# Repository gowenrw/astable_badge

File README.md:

# astable_badge
BSidesDFW 2021 Badge - Astable Multivibrator - Learn To Solder/Electronics/DIY

This is where all the files for the astable_badge will be stored.  
This includes code and art and cad and fab files.  All the things.

## File Structure

This is the file structure of this repository

* [/](/README.md) - YOU ARE HERE
* [/art/](./art/) - Artwork and other graphics created by this project
* [/code/](./code/) - All project related Code / Firmware
* [/docs/](./docs/) - Documentation created by this project including web pages
* [/eda/](./eda/) - Electronic Design Automation files (i.e. KiCad)
* [/reference_parts/](./reference_parts/) - Documentation pulled from other sources related to components (this is a submodule, see below)
* [./README.md](/README.md) - This File
* [./LICENSE](/LICENSE) - Currently set to MIT

Note: the reference_parts directory a link to a submodule repository.
To add it use the following cmd after downloading this template:
```
git submodule add https://github.com/gowenrw/reference_parts reference_parts
```
This will make a link to the current commit of that repo.
To update it to a newer commit after its been added use this cmd:
```
git submodule update --recursive
```

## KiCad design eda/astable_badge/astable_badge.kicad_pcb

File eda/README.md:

# Electronic Design Automation

This is where all the Electronic Design Automation files for the PCB(s) will be stored.
The EDA used is KiCad 5.x unless otherwise specified.

The KiCad projects have been configured to use local libraries for long term sustainability per the best practices listed [HERE](https://hackaday.com/2017/05/18/kicad-best-practises-library-management/) and elsewhere.

## File Structure

This is the file structure of this repository

* [/](/README.md) - Home
* [/eda](/eda/) - YOU ARE HERE
  * /eda/astable_badge/ - KiCad project folder for the badge PCB
    * ./3d_models/ - This directory contains footprint 3d model files
    * ./gerber/ - This directory contains gerber formatted files for manufacturing
    * ./lib_fp/ - This directory contains footprint module directories
    * ./lib_sh/ - This directory contains schematic library files
    * ./snapshots/ - This directory contains prints of schematic / cad files and images of preview / final product
  * /eda/astable_dev/ - KiCad project folder for the development PCB
    * ./3d_models/ - This directory contains footprint 3d model files
    * ./gerber/ - This directory contains gerber formatted files for manufacturing
    * ./lib_fp/ - This directory contains footprint module directories
    * ./lib_sh/ - This directory contains schematic library files
    * ./snapshots/ - This directory contains prints of schematic / cad files and images of preview / final product

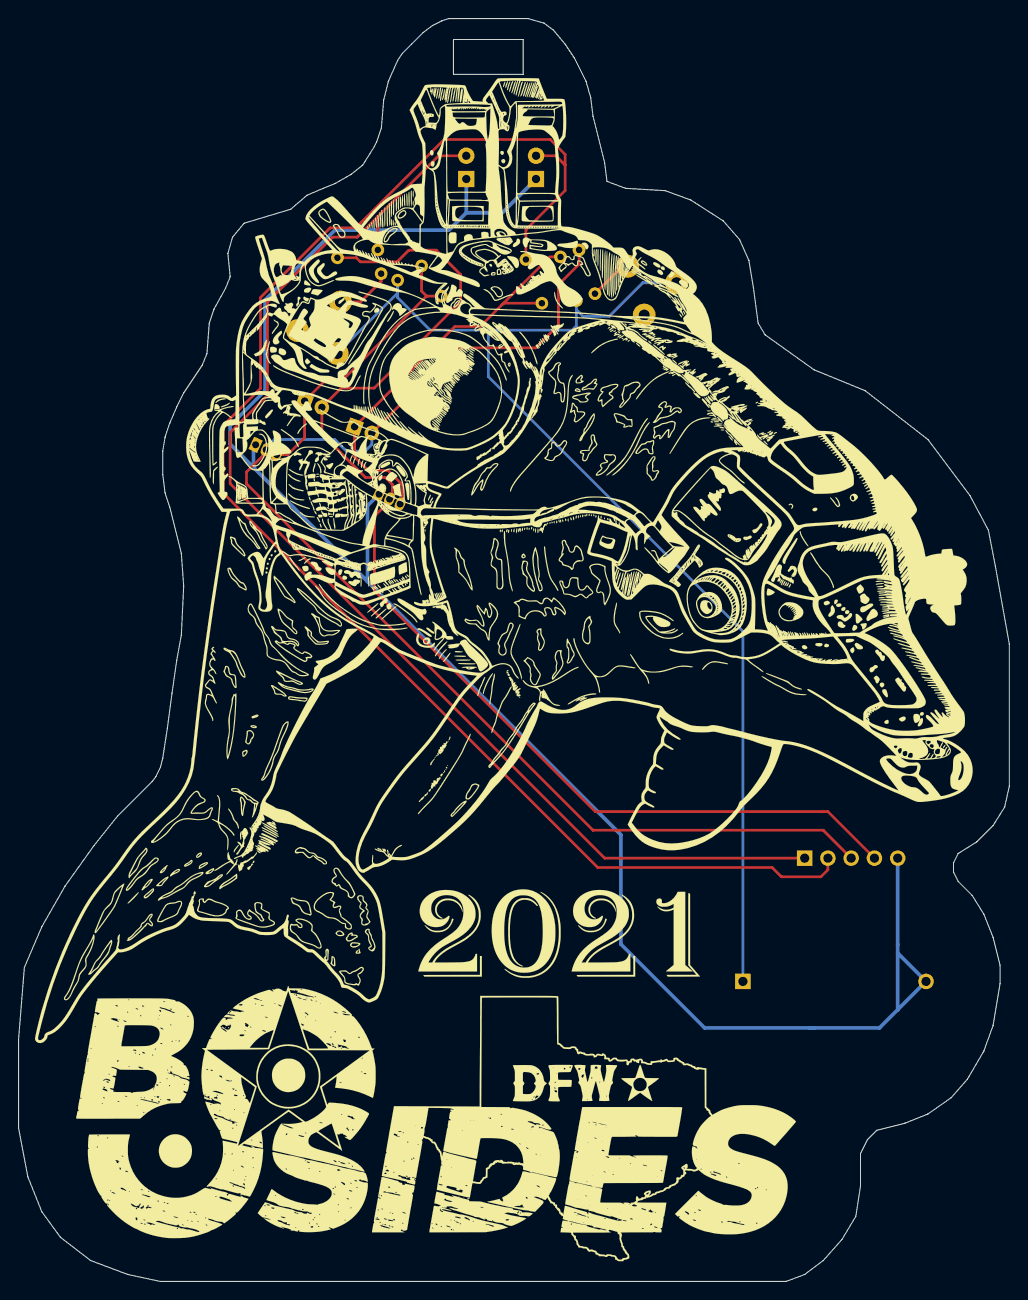
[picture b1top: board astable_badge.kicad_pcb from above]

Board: 2 copper layers, 108.2 x 137.9 mm, 16 parts (0 on the bottom side), 10 nets.

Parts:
BT1: CR2032 3V; BatteryHolder_CR2032-BS-2-1_Front_backsilk
C1, C2: 100 uF; CP_Radial_D5.0mm_P2.00mm_backsilk
D1, D2: LED; LED_D3.0mm-2_backsilk
Q1, Q2: 2N2222A; Q_2222A_TO-92_Inline_back-silk
R1, R2: 1K R; R_Axial_DIN0204_L3.6mm_D1.6mm_P5.08mm_Horizontal_backsilk
R3, R4: 510 R; R_Axial_DIN0204_L3.6mm_D1.6mm_P5.08mm_Horizontal_backsilk
R5, R6: 10 R; R_Axial_DIN0204_L3.6mm_D1.6mm_P5.08mm_Horizontal_backsilk
RV1, RV2: 0-30K Ohms; R_Potentiometer_3pin_THT_5mm_backsilk_anno
TPJ1: Test Point Connector; Conn_Pin_Header_Hole_1x05_Pitch2.54mm

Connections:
GND: BT1.2, D1.1, D2.1, Q1.1, Q2.1, TPJ1.5
unnamed: BT1.1, R3.1, R4.2, RV1.3, RV2.3
unnamed: C1.1, Q1.3, R3.2, R5.2
unnamed: C2.1, Q2.3, R4.1, R6.1
unnamed: R1.1, RV1.2
unnamed: R2.2, RV2.2
TP1: D1.2, R5.1, TPJ1.1
TP2: D2.2, R6.2, TPJ1.2
TP3: C2.2, Q1.2, R2.1, TPJ1.3
TP4: C1.2, Q2.2, R1.2, TPJ1.4

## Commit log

2021-08-17 initial template push
2021-08-17 eda initial file layout
2021-08-18 Added schematic symbols and footprints
2021-08-19 dev board complete
2021-10-04 Principal Art Work
2021-10-04 Preparing badge EDA
2021-10-20 Final badge art and EDA updates.
2021-10-21 cleanup and doc prep
2021-10-26 Documentation updates
2021-10-26 updates for web page
2021-10-27 web page instructions updated
2021-10-27 minor corrections to instructions
